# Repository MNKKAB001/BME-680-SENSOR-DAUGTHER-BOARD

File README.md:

# BME-680-SENSOR-DAUGTHER-BOARD
The design of the project was to create a sensor for a raspberry pi, microprocessor which contains different GPOI pins up to 40 of the pin the main pins that the user will mainly use is the I2C pin, SDA I2C, SCL I2C and the power pin of 3v3  which are the connected to the daughter board via female to female wire which the configures the communication, using a python code the BME can easily communicate with the raspberry pi zero w, the sensor is known as multisensory board since it can sense different environmental aspect like humidity, temperature and pressure.  

Ki-Cad software was used to model and simulate the design by identifying the requirements for the circuits which were BME680, Capacitors and Connector wire 2 attempts were made when schematic was under design firstly connections were made directly to the BME component which might lead to the fluctuation of temperature and high frequency disturbance resulting into incorrect configuration and resulting and failure which might damage the circuit the error checking was done using the ERC in ki-cad  which provided error and warning from the schematic design.
Second attempt was to compensate the connection through a connector that is placed parallel to the BME and configured the pins and 2 capacitors were then connected through the VDD and VDDIO to filter any unwanted noise from the environment the diagram below show the design and error checking

Various design model were consider waterfall, spiral and agile but due the complexity of the design the best model that was considered was agile as it involves frequent error checking and changes of requirements and specification by producing different PCB design and testing the PCB required had to fall under a certain measurement which include the dimension of the board that is 25mm x 25mm which is a very good size for a daughter board and  weight of the board was also considered which meant restrictions were introduced through adding different layers in our PCB and not adding to many components that might lead to much power consumption.

The design was a success due to meeting most of the design requirements and running sufficient testing for the BME board sensor this included two major test which were ERC and DRC for the board and extra testing was also done in LT-Spice simulation for extra verification purpose

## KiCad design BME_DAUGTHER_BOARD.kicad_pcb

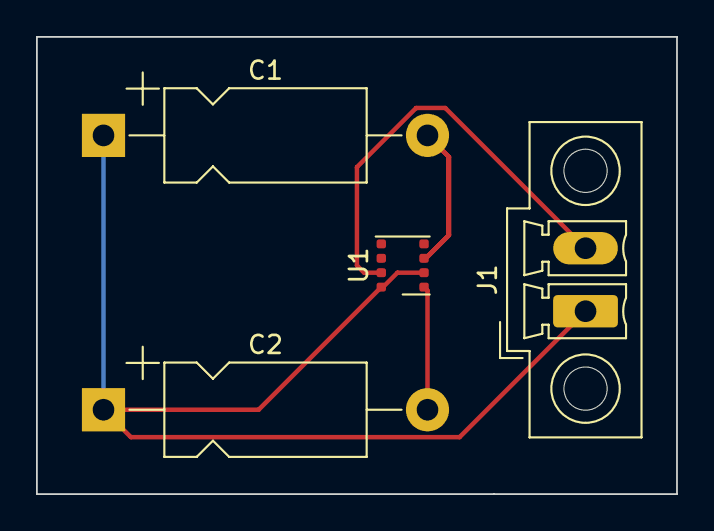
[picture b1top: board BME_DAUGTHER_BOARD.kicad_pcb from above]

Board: 2 copper layers, 35.6 x 25.4 mm, 4 parts (0 on the bottom side), 4 nets.

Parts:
C1, C2: 0.1uF; CP_Axial_L11.0mm_D5.0mm_P18.00mm_Horizontal
J1: Conn_01x08_Male; PhoenixContact_MCV_1,5_2-GF-3.5_1x02_P3.50mm_Vertical_Threa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
U1: BME680; Bosch_LGA-8_3x3mm_P0.8mm_ClockwisePinNumbering

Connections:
CSB: J1.2, U1.2 (CSB)
unnamed: C1.2, U1.6 (VDDIO)
unnamed: C2.2, U1.8 (VDD)
VDD: C1.1, C2.1, J1.1, U1.1 (GND), U1.7 (GND)

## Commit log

2022-06-03 Design File
    Design Files
2022-06-03 Gerber file
    version 1 garber
2022-06-03 Testing PCB and Schematics
    Test version
2022-06-03 Specification
    Meeting Specifation
2022-06-08 Update README.md
    proofreading and error fixing
